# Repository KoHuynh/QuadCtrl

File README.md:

<p align="center">
  <picture>
    <source media="(prefers-color-scheme: dark)" srcset="./images/quadctrl_logo_white_transparent.png">
    
  </picture>
</p>

<p align="center">

  <!-- Laptop app, flight logger, simulation -->
  
  <!-- Hardware & mechanical -->
  
</p>

**A low-cost micro-quadcopter that makes avionics and flight-control education accessible.**

---

QuadCtrl is a ~$30 educational micro-quadcopter designed to teach embedded flight control from the ground up. An ESP32-S3 flight controller fuses LSM6DSV IMU data with a complementary filter and runs a cascaded angle → rate PID loop at 500 Hz to drive four 8520 brushed motors. A custom ESP-NOW transmitter with an OLED display and potentiometers lets you tune PID gains live, in flight. A VL53L0X/VL53L1X time-of-flight sensor adds altitude hold, and optical flow and UWB positioning are planned for autonomous flight without motion capture.

---

# Contents

- [Features](#features)
- [Hardware](#hardware)
- [Electronics](#electronics)
- [Flight Control Algorithm](#flight-control-algorithm)
  - [1. Feedback Control Basics](#1-feedback-control-basics)
  - [2. Attitude Estimation](#2-attitude-estimation)
  - [3. Pilot Commands and Motor Mixing](#3-pilot-commands-and-motor-mixing)
  - [4. Cascaded PID Control](#4-cascaded-pid-control)
  - [5. Altitude Hold](#5-altitude-hold)
- [Roadmap](#roadmap)
- [Acknowledgments](#acknowledgments)

---

# Features

- **500 Hz cascaded PID control**: an outer angle loop feeds an inner rate loop on roll and pitch, with heading hold on yaw
- **Complementary-filter attitude estimation**, with low-pass filtering on the gyro and accelerometer
- **Custom ESP-NOW transmitter** with live PID tuning (potentiometers), flight trim, an OLED telemetry display, and arming safety
- **Altitude hold** using a downward-facing time-of-flight sensor fused with the accelerometer
- **Safety features**: link-loss failsafe (auto-land in altitude mode), attitude cutoff, low-battery monitoring, and throttle-low arming
- **Low cost and simple to build**: off-the-shelf parts, a custom shield PCB, and a 3D-printed frame

# Hardware

| Component | Details |
|---|---|
| Microcontroller | ESP32-S3 dev board (EnVision Maker Studio) with a custom drone shield |
| IMU | LSM6DSV 6-axis accelerometer + gyroscope (I²C) |
| Motors | 4 × 8520 coreless brushed DC motors |
| Propellers | 75 mm |
| Battery | 1S LiPo (660 mAh), roughly 5–7 minutes of flight |
| Height sensor | VL53L0X / VL53L1X time-of-flight (auto-detected) |
| Frame | 3D-printed motor-mount frame |
| Weight | ~75 g |
| Radio | ESP-NOW (2.4 GHz) to a custom ESP32-S3 transmitter |

---

# Electronics

The full shield schematic is available here: [ECE193HQuadCopterShieldSchematicV1.pdf](./images/ECE193HQuadCopterShieldSchematicV1.pdf)

Each motor is driven by a low-side MOSFET switch. The key components are:

- **N-channel MOSFET**: acts as a voltage-controlled switch. When the ESP32 drives the gate HIGH (e.g. GPIO 4), the MOSFET turns on and current flows through the motor. Motor speed is set by the PWM duty cycle (20 kHz).
- **Gate pull-down resistor (10 kΩ)**: holds the MOSFET off whenever the gate is not being actively driven, such as during boot or reset, so the motors cannot spin unexpectedly.
- **Flyback diode (Schottky)**: a motor winding is an inductor, and its current cannot change instantaneously. When the MOSFET switches off, the diode gives that current a safe path to circulate back through the motor and decay. Without it, the resulting voltage spike could destroy the MOSFET. A Schottky diode is used because it switches fast enough to keep up with the PWM.
- **Bulk capacitor (220 µF)**: the motors draw large current bursts, especially at start-up. The battery and its wiring cannot respond instantly, so the bulk capacitor supplies these bursts locally and limits supply dips that could brown out the microcontroller.
- **Bypass capacitor (1 µF)**: shunts high-frequency noise generated by the motors to ground, keeping the supply clean for the logic and sensors.

Battery monitor: A voltage divider made of two 100 kΩ resistors halves the battery voltage, $V_{sense} = V_{bat}\cdot\frac{R_2}{R_1+R_2} = \frac{V_{bat}}{2}$, so a full 4.2 V cell reads 2.1 V, safely within the ESP32-S3’s ADC range. The firmware multiplies the reading by 2 to recover $V_{bat}$ and drives three status LEDs: green (≥ 3.80 V), yellow (3.50–3.80 V), and red (< 3.50 V, recharge soon). The high resistor values keep the divider’s drain to about 21 µA.

---

# Flight Control Algorithm

This section gives an overview of how QuadCtrl stays level and responds to commands. Some familiarity with feedback control helps, but it is not required.

### 1. Feedback Control Basics

A typical closed-loop system works like this:

1. The **reference** $r(t)$ is the desired output, such as a target angle.
2. A **summing node** compares the reference with the sensor measurement to produce the **error**, $e(t) = r(t) - y(t)$.
3. The **controller** turns the error into a command for the **actuators**. Here, the controller decides how hard each motor should spin.
4. The actuators drive the **plant**: the system being controlled, which here is the drone, with its own mass, inertia, and dynamics.
5. The plant's output (angle, rate, height, …) is measured by the **sensors** and fed back to the summing node. The loop repeats continuously to drive the error toward zero.

### 2. Attitude Estimation

To stay level, the drone must first know its orientation (attitude). The LSM6DSV IMU provides two measurements:

- **Gyroscope**: angular rate (°/s) about each axis. On this board, roll is rotation about the forward (y) axis, pitch is rotation about the right (x) axis, and yaw is rotation about the vertical (z) axis.
- **Accelerometer**: linear acceleration plus gravity, which tells the drone which way is down.

**Calibration.** At power-up the drone must sit still while the firmware measures the gyroscope's resting offset (bias). This offset is subtracted from every later reading. A separate level calibration stores the accelerometer's "level" reference in flash.

**Filtering.** Motor vibration adds noise to both sensors. The gyro rates pass through an 80 Hz second-order Butterworth low-pass filter, and the accelerometer uses the IMU's built-in digital low-pass filter (~24 Hz).

**Gyroscope integration.** Integrating the angular rate gives an angle estimate, the same way integrating velocity gives position:

$$\theta(t) = \theta(0) + \int_0^t \omega(\tau)\,d\tau$$

This estimate is smooth and responds instantly. However, any small bias in $\omega$ is integrated as well, so the angle error grows steadily over time (drift).

**Accelerometer tilt.** At rest, the accelerometer measures only gravity. When the drone tilts, gravity is split across the axes, and trigonometry recovers the tilt angle. This reference never drifts, but it is unreliable over short timescales. Any real acceleration, such as sliding sideways, mixes with gravity and makes the drone appear tilted.

**Complementary filter.** The two estimates have opposite strengths, so they are blended every loop:

$$\theta_k = \alpha\,(\theta_{k-1} + \omega_k\,\Delta t) + (1-\alpha)\,\theta_{\text{accel},k}, \qquad \alpha = \frac{\tau}{\tau + \Delta t}$$

With a time constant $\tau = 2$ s and $\Delta t = 2$ ms, $\alpha \approx 0.999$. Each step, the gyro predicts the new angle, and the estimate is nudged slightly toward the accelerometer's gravity angle. Both sensors contribute at all times rather than handing off. Changes faster than about 2 s come from the gyro, while slow drift is pulled out by the accelerometer.

**Limitation: position.** Gravity gives an absolute reference for *tilt*, but nothing in the IMU gives an absolute reference for *position*. Estimating position means integrating acceleration twice, so errors grow with $t^2$, and the IMU alone cannot tell where the drone is in the room. Holding position requires external sensing such as optical flow or UWB (see [Roadmap](#roadmap)).

### 3. Pilot Commands and Motor Mixing

The transmitter sends stick positions to the drone over ESP-NOW at 50 Hz:

- **Roll / pitch sticks** set a target tilt angle (up to ±20°). Trim adds a small constant offset to cancel a steady drift. For example, if the drone always drifts right, trim adds a slight constant left command.
- **Yaw stick** sets a target turn rate.
- **Throttle** sets the base thrust in manual mode, or the target height in altitude-hold mode.

The controller's corrections are mixed into the four motors (X configuration):

- **Pitch**: speed up one pair (front or rear) and slow the other.
- **Roll**: speed up one side (left or right) and slow the other. For example, to move left, the right-side motors speed up, the drone tilts left, and part of the thrust pushes it left. Once the target tilt is reached, the motors even out to hold that angle.
- **Yaw**: speed up one diagonal pair and slow the other. Diagonal motors spin in the same direction, so this changes the net reaction torque on the frame and rotates it without tilting.

When a correction would push a motor above 100 %, all motors are lowered together (desaturation) so the differences between them, and therefore stability, are preserved.

### 4. Cascaded PID Control

QuadCtrl uses two nested loops per axis rather than one. The gyroscope measures rotation rate directly and quickly, so a fast inner loop can reject disturbances immediately. The slower outer loop only has to decide how fast the drone should rotate toward its target angle. Splitting the job this way is more stable and easier to tune than a single loop.

**Outer loop: angle control (P).** The angle error (target − estimate) is multiplied by a gain to produce a desired rotation rate. With a gain of 3, a nose that is 5° too high commands a 15°/s nose-down rotation. Yaw uses heading hold: the stick moves a heading setpoint, and any heading error, such as from a bump, becomes extra yaw rate that turns the nose back.

**Inner loop: rate control (PID).** Each axis compares the desired rate with the gyro's measured rate:

- **P (proportional)** reacts to the current error: the further off it is, the harder it corrects.
- **I (integral)** accumulates error over time to cancel steady biases such as an off-center battery or a weaker motor.
- **D (derivative)** reacts to how fast the error is changing, damping the response so it doesn't overshoot.

The output is a correction for each axis, expressed as a percentage of motor power, which is sent to the motor mixer. Roll and pitch rate gains can be tuned live from the transmitter's potentiometers.

### 5. Altitude Hold

With a downward-facing time-of-flight sensor, the throttle stick becomes a **height command** (e.g. 10 % → 0.2 m, 100 % → 1.0–1.5 m):

1. **Height estimation**: a vertical complementary filter fuses the accelerometer (fast, but drifts) with the ToF range (slow, noisy, but drift-free). The ToF range is tilt-corrected as $h = r\cos\phi\cos\theta$.
2. **Height → climb rate (P)**: height error is converted into a target vertical speed, limited to 0.5 m/s.
3. **Climb rate → throttle (PI)**: the integral term converges to the hover throttle. It is learned during flight and saved, which also compensates for battery sag automatically.

Altitude mode also includes automatic landing, auto-land on radio link loss, and a controlled descent if the height sensor's readings are lost.

---

# Roadmap

- [x] Stabilized flight with cascaded PID
- [x] Live PID tuning and trim from the transmitter
- [x] Altitude hold (VL53L0X / VL53L1X)
- [ ] Optical flow velocity hold (PMW3901) to eliminate horizontal drift
- [ ] UWB positioning (DWM3000) for waypoint navigation without motion capture
- [ ] Multi-drone coordinated flight
- [ ] ToF Ring Sensor -> SLAM
- [ ] Brushless Motor Version for more stable outdoor flight
- [ ] GPS, RTK -> Drone Shows w/ RGB Lights Add-On

### Time-of-Flight Rangefinder: Indoor Altitude Hold

A ToF sensor fires short pulses of invisible (940 nm, eye-safe) infrared laser light at the floor and measures how long the reflection takes to return. Since light travels at a known speed, the round-trip time gives the distance:

$$d = \frac{c \cdot t_{\text{round trip}}}{2}$$

Because the drone tilts while flying, the beam hits the floor at a slant, so the reading is corrected to a true vertical height: $h = d\cos\phi\cos\theta$ (roll $\phi$, pitch $\theta$).

**How it is used:** the ToF height is fused with the accelerometer. The ToF is drift-free but slow and noisy (~30 Hz); the accelerometer is fast but drifts. The result is a smooth height and climb-rate estimate. In altitude-hold mode, the **throttle stick becomes a height command** instead of raw thrust. A height loop converts height error into a target climb rate. A climb-rate PI loop then adjusts throttle around the hover point, and its integral term learns the hover throttle automatically.

**Limits:** range of ~1–2 m (VL53L0X) to ~3–4 m (VL53L1X) indoors. Readings degrade in bright sunlight and over very dark or reflective surfaces. A table or step under the drone looks like a sudden change in height.

---

### Barometer (BMP581): Outdoor Altitude Hold

Air pressure decreases as you climb, by about **12 Pa per meter** near sea level. A barometer measures this pressure, and the change since takeoff gives the height *relative* to the takeoff point:

$$h \approx 44330 \left[1 - \left(\frac{P}{P_0}\right)^{1/5.255}\right] \text{ m}$$

where $P_0$ is the pressure measured on the ground before takeoff.

**Why outdoors:** a ToF sensor runs out of range after a few meters, while a barometer works at any height. The BMP581 resolves height changes of roughly ±0.5 m (or better with filtering), which is fine for holding altitude in open air. As with the ToF, the barometer is fused with the accelerometer for a smooth estimate, and it feeds the same altitude-hold controller.

**Limits:** it measures only relative height, and weather changes slowly shift the reference. Propeller downwash and wind gusts cause pressure noise, so the sensor should be shielded with a small piece of foam. It is much less precise than a ToF sensor close to the ground.

---

### Optical Flow Sensor: Indoor Horizontal Position Hold

An optical flow sensor is a tiny, low-resolution camera that takes hundreds of frames per second. It compares consecutive frames internally and outputs how far the image of the floor has shifted, in pixels ($\Delta x, \Delta y$). Dividing by the time between readings gives **pixels per second**: how fast the floor *appears* to slide past.

Each pixel covers a fixed viewing angle (about 1° on a PMW3901), so this "optical flow" is really an **angular rate**: how many radians per second the floor sweeps across the view. The same ground speed looks slower the higher you fly, just as distant objects seem to move slowly from a car window. **That is why height is required**. Multiplying by the ToF height converts flow into real velocity:

$$v \approx (\omega_{\text{flow}} - \omega_{\text{gyro}}) \cdot h$$

The gyro term is important. When the drone simply tilts in place, the floor *appears* to move even though the drone has not translated, so the measured rotation rate is subtracted first.

**How it is used:** with velocity known, a new outer control loop commands tilt angles that drive horizontal velocity to zero when the sticks are centered. This cancels the slow drift that the IMU alone cannot detect.

**Limits:** it needs a textured, well-lit floor; plain or glossy floors and dim rooms fail. It only works within a limited height range (a PMW3901 needs at least ~8 cm). It measures velocity, not absolute position, so small errors still accumulate into slow wandering over time.

---

### GPS + Magnetometer (u-blox SAM-M10Q): Outdoor Position Hold

Optical flow becomes unreliable at greater heights and over uniform outdoor ground such as grass or pavement. Outdoors, GPS provides an **absolute** position that does not drift over time. This matters for holding position and for coordinating multiple drones.

A **magnetometer** (digital compass) is needed alongside GPS. The gyro's yaw estimate slowly drifts, but to correct a position error the drone must know which way its nose points, so it can decide which direction to tilt. The magnetometer provides that absolute heading.

**Limits:**
- **Accuracy:** a standard module like the [SAM-M10Q](https://www.digikey.com/en/products/detail/u-blox/SAM-M10Q-00B/16672678) is accurate to about **1.5–2 m**. That is fine for a single drone loitering in place, but not for drones flying close together; that requires RTK GPS (centimeter-level).
- **Update rate:** GPS updates slowly (a few Hz), so it is fused with the IMU for smooth control.
- **Magnetic interference:** motor currents and the battery distort the magnetometer, so it must be mounted away from power wiring and calibrated.
- **Weight and wind:** a ~75 g brushed drone struggles in outdoor wind, so outdoor GPS work is best suited to a future **brushless** version of QuadCtrl.

---

### RGB Light Shield: Drone Light Shows

With a ring of RGB LEDs under a translucent diffuser shell, each drone becomes a single glowing "pixel" when seen from a distance at night. With enough drones, each holding a precise position, the swarm can draw shapes and images in the sky.

Beyond the lights themselves, a light show requires:
- **Precise positioning**: RTK GPS (centimeter-level), since standard GPS is too coarse for drones flying meters apart
- **Time synchronization**: every drone must execute its path at exactly the right moment, and GPS conveniently provides an accurate time reference
- **Choreography software**: converts a target image or animation into a collision-free 3D path for each drone
- **Regulatory approval**: in the US, one pilot or ground station operating multiple drones requires an FAA Part 107 waiver (§107.35)

---

### UWB Positioning (DWM3000): Indoor Swarm Flight

Ultra-wideband (UWB) radio is the indoor counterpart to GPS. Several fixed **anchors** are placed around the room, and the drone carries a **tag**. The tag measures its distance to each anchor by timing radio messages, either by two-way ranging or by time-difference-of-arrival. It then trilaterates its position to about **10 cm**, with at least four anchors needed for 3D.

This is the approach used by Bitcraze's Loco Positioning System for the Crazyflie. Because every drone shares the same anchor coordinate frame, UWB enables **indoor waypoint navigation and coordinated multi-drone (swarm) flight** without an expensive motion-capture system.

**Limits:** the anchors must be installed and surveyed, and accuracy degrades when walls or people block the line of sight. Each module adds weight and power draw (~40–55 mA while active). Optical flow is still useful alongside UWB for smooth, low-noise velocity.

---

### Obstacle Sensing (Lidar / Multi-Zone ToF): Toward Autonomous Flight

To navigate autonomously, the drone must sense its surroundings, not just the floor. Options, from heaviest to lightest:

- **2D 360° lidar** (e.g. LD06/LD19, RPLIDAR C1): a spinning laser that measures distance all the way around the drone, producing a horizontal "slice" of the room. These weigh roughly 40–110 g, too much for the current brushed frame, so they suit a larger brushless version.
- **Multiple ToF sensors**: four or five VL53L1X sensors facing front, back, left, right, and up. This is the approach of the Crazyflie **Multi-ranger deck**: lightweight and simple, but with only one distance per direction.

- **Multi-zone ToF (VL53L5CX)**: a single tiny sensor that returns an **8×8 grid of distances** over a ~63° field of view, like a very coarse depth camera.

**2.5D, not 3D:** a 2D lidar combined with the downward ToF height sensor gives a horizontal map of the room plus the drone's altitude. This is often called "2.5D". It is not a full 3D map, so obstacles above or below the scan plane can be missed.

**Toward SLAM:** distance scans combined with motion estimates (optical flow and IMU) are the inputs to **SLAM** (Simultaneous Localization and Mapping). In SLAM, the drone builds a map of an unknown room while tracking its own position within that map. Because SLAM is computationally heavy, it would likely run on a laptop or companion computer, with sensor data streamed from the drone and commands sent back.

---

# Acknowledgments

QuadCtrl was inspired by UCSD's **CSE 176E/276E** course taught by **Professor Steven Swanson**. The goal of this project is to streamline that design around the **EnVision Maker Studio ESP32-S3 dev board**. Several filtering and control ideas, such as the 80 Hz gyro filter and yaw heading hold, were informed by the open-source Crazyflie and LiteWing flight firmware.

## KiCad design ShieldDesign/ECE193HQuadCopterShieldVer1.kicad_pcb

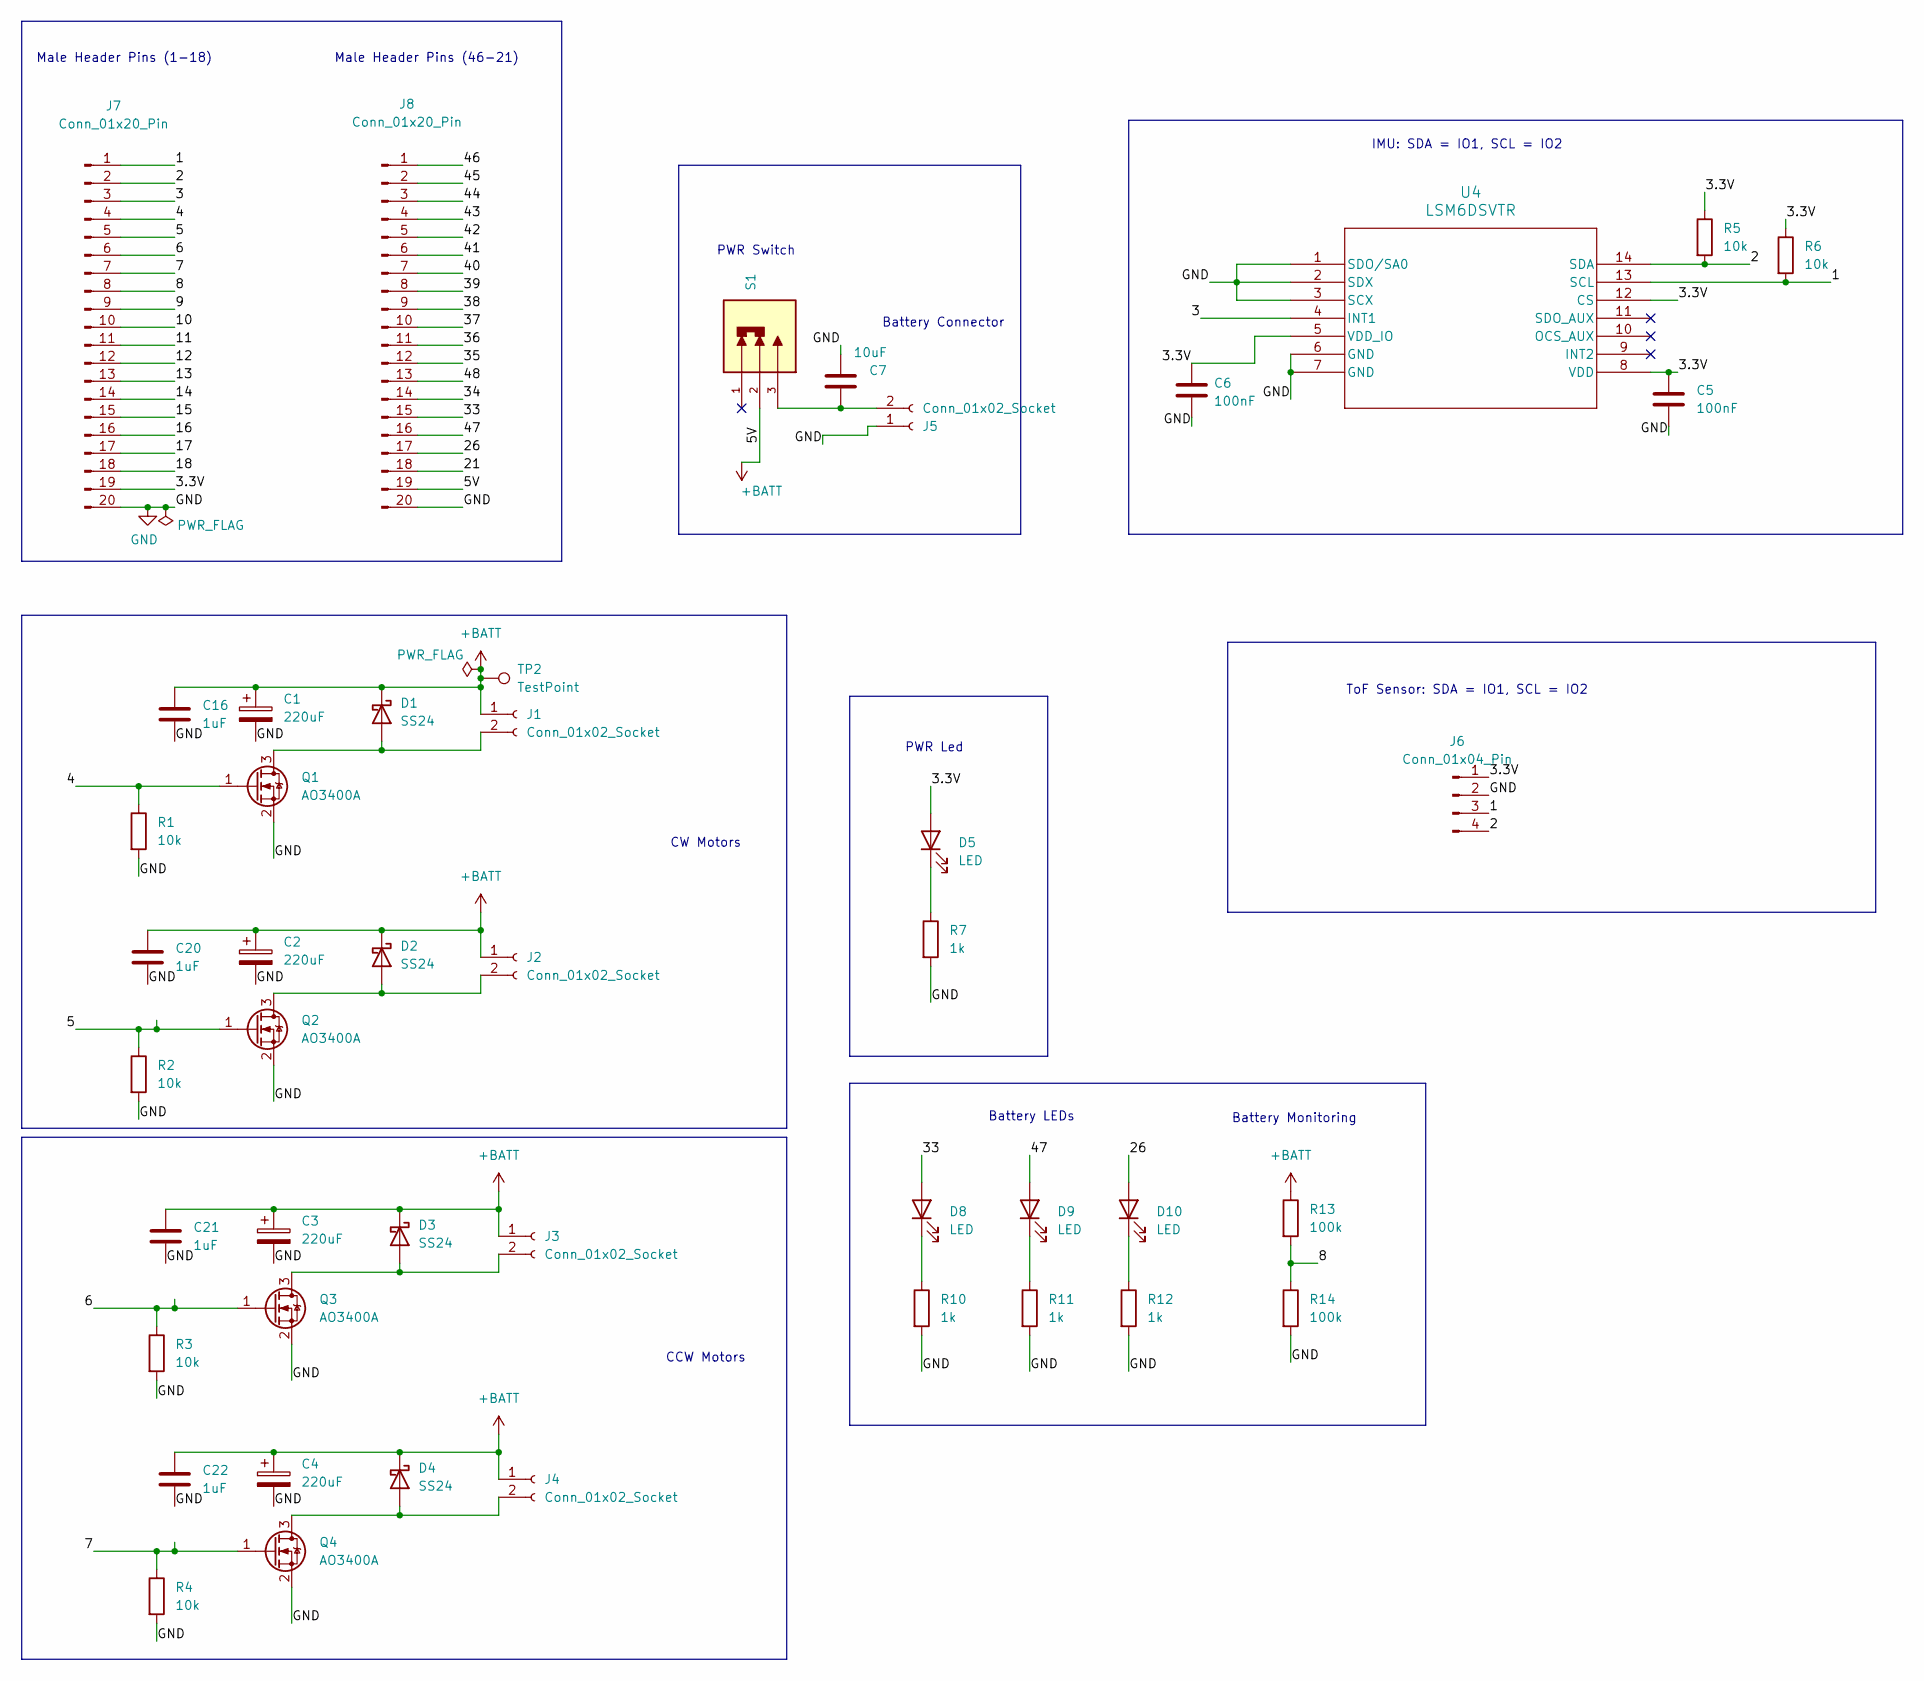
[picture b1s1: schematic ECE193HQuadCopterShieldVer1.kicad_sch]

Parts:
C1, C2, C3, C4: 220uF; CAP_EEEFK1A221SL
C5, C6: 100nF; C_0805_2012Metric_Pad1.18x1.45mm_HandSolder
C7: 10uF; C_0805_2012Metric_Pad1.18x1.45mm_HandSolder
C16, C20, C21, C22: 1uF; C_0805_2012Metric
D1, D2, D3, D4: SS24; D_SMA
D5, D8, D9, D10: LED; LED_0805_2012Metric
J1, J2, J3, J4, J5: Conn_01x02_Socket; PinHeader_1x02_P2.54mm_Vertical
J6: Conn_01x04_Pin; PinHeader_1x04_P2.54mm_Vertical
J7, J8: Conn_01x20_Pin; PinHeader_1x20_P2.54mm_Vertical
Q1, Q2, Q3, Q4: AO3400A; SOT-23
R1, R2, R3, R4, R5, R6: 10k; R_0805_2012Metric_Pad1.20x1.40mm_HandSolder
R7, R10, R11, R12: 1k; R_0805_2012Metric_Pad1.20x1.40mm_HandSolder
R13, R14: 100k; R_0805_2012Metric_Pad1.20x1.40mm_HandSolder
S1: SLW-105558-2A-N-D; SW_SLW-105558-2A-N-D; PARTREV 1.01
TP2: TestPoint; TestPoint_Pad_D1.0mm
U4: LSM6DSVTR; LGA14-L_2P59X3P1X0P5_STM

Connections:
+BATT: C1.1, C2.1, C3.1, C4.1, C16.1, C20.1, C21.1, C22.1, D1.1 (K), D2.1 (K), D3.1 (K), D4.1 (K), J1.1, J2.1, J3.1, J4.1, J8.19, R13.1, S1.2, TP2.1; also elsewhere on the board
/1: J6.3, J7.1, R6.2, U4.13 (SCL)
/2: J6.4, J7.2, R5.2, U4.14 (SDA)
/3: J7.3, U4.4 (INT1)
/3.3V: C5.1, C6.1, D5.2 (A), J6.1, J7.19, R5.1, R6.1, U4.5 (VDD_IO), U4.8 (VDD), U4.12 (CS)
/4: J7.4, Q1.1 (G), R1.1
/5: J7.5, Q2.1 (G), R2.1
/6: J7.6, Q3.1 (G), R3.1
/7: J7.7, Q4.1 (G), R4.1
/8: J7.8, R13.2, R14.1
/9: J7.9
/10: J7.10
/11: J7.11
/12: J7.12
/13: J7.13
/14: J7.14
/15: J7.15
/16: J7.16
/17: J7.17
/18: J7.18
/21: J8.18
/26: D10.2 (A), J8.17
/33: D8.2 (A), J8.15
/34: J8.14
/35: J8.12
/36: J8.11
/37: J8.10
/38: J8.9
/39: J8.8
/40: J8.7
/41: J8.6
/42: J8.5
/43: J8.4
/44: J8.3
/45: J8.2
/46: J8.1
/47: D9.2 (A), J8.16
/48: J8.13
GND: C1.2, C2.2, C3.2, C4.2, C5.2, C6.2, C7.2, C16.2, C20.2, C21.2, C22.2, J5.1, J6.2, J7.20, J8.20, Q1.2 (S), Q2.2 (S), Q3.2 (S), Q4.2 (S), R1.2, R2.2, R3.2, R4.2, R7.2, R10.2, R11.2, R12.2, R14.2, U4.1 (SDO/SA0), U4.2 (SDX), U4.3 (SCX), U4.6 (GND), U4.7 (GND)
unnamed: D1.2 (A), J1.2, Q1.3 (D)
unnamed: D2.2 (A), J2.2, Q2.3 (D)
unnamed: D3.2 (A), J3.2, Q3.3 (D)
unnamed: D4.2 (A), J4.2, Q4.3 (D)
unnamed: D5.1 (K), R7.1
unnamed: D8.1 (K), R10.1
unnamed: D9.1 (K), R11.1
unnamed: D10.1 (K), R12.1
unnamed: C7.1, J5.2, S1.3

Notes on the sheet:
ToF Sensor: SDA = IO1, SCL = IO2
Male Header Pins (46-21)
CW Motors
IMU: SDA = IO1, SCL = IO2
Battery LEDs
PWR Switch
Battery Connector
PWR Led
CCW Motors
Battery Monitoring
Male Header Pins (1-18)

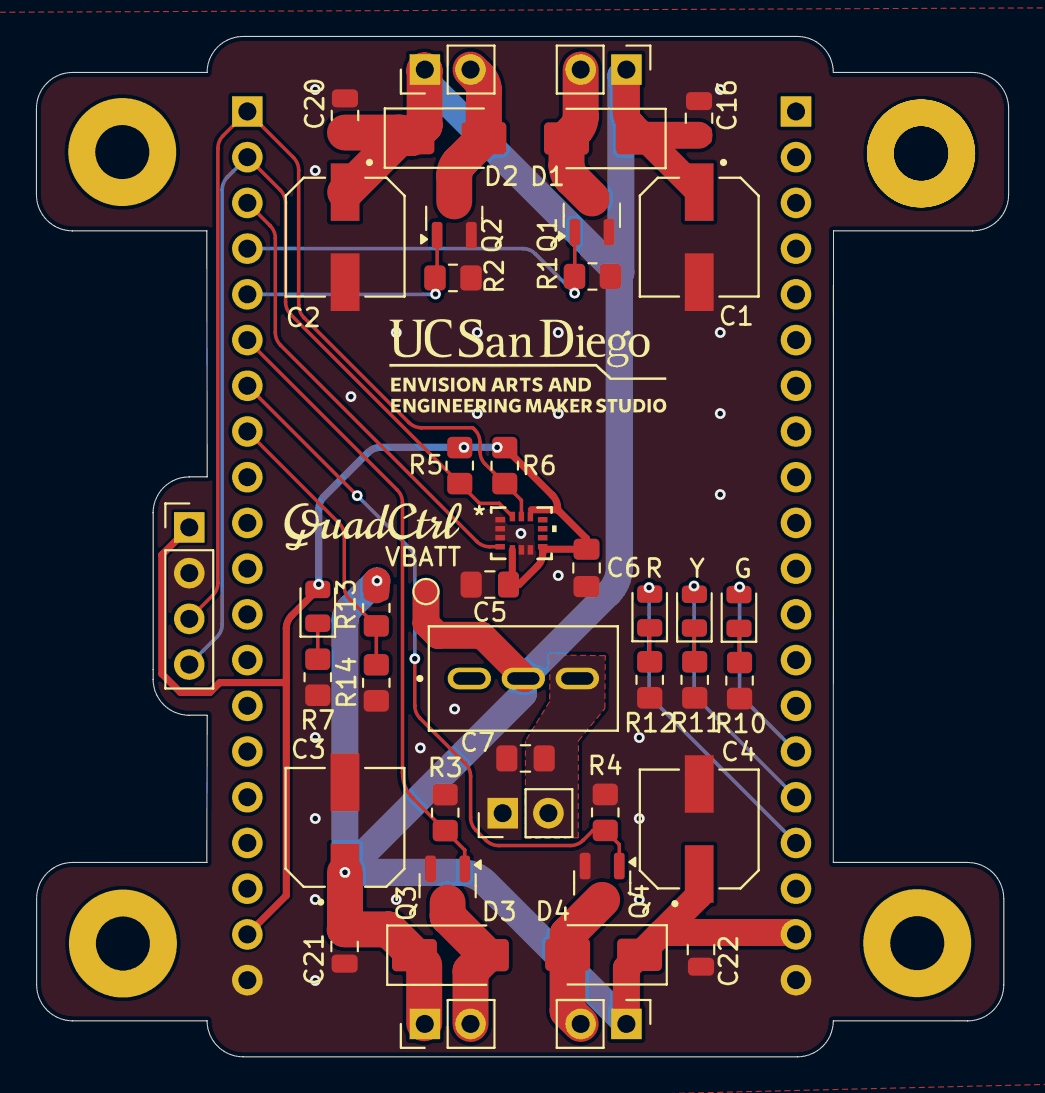
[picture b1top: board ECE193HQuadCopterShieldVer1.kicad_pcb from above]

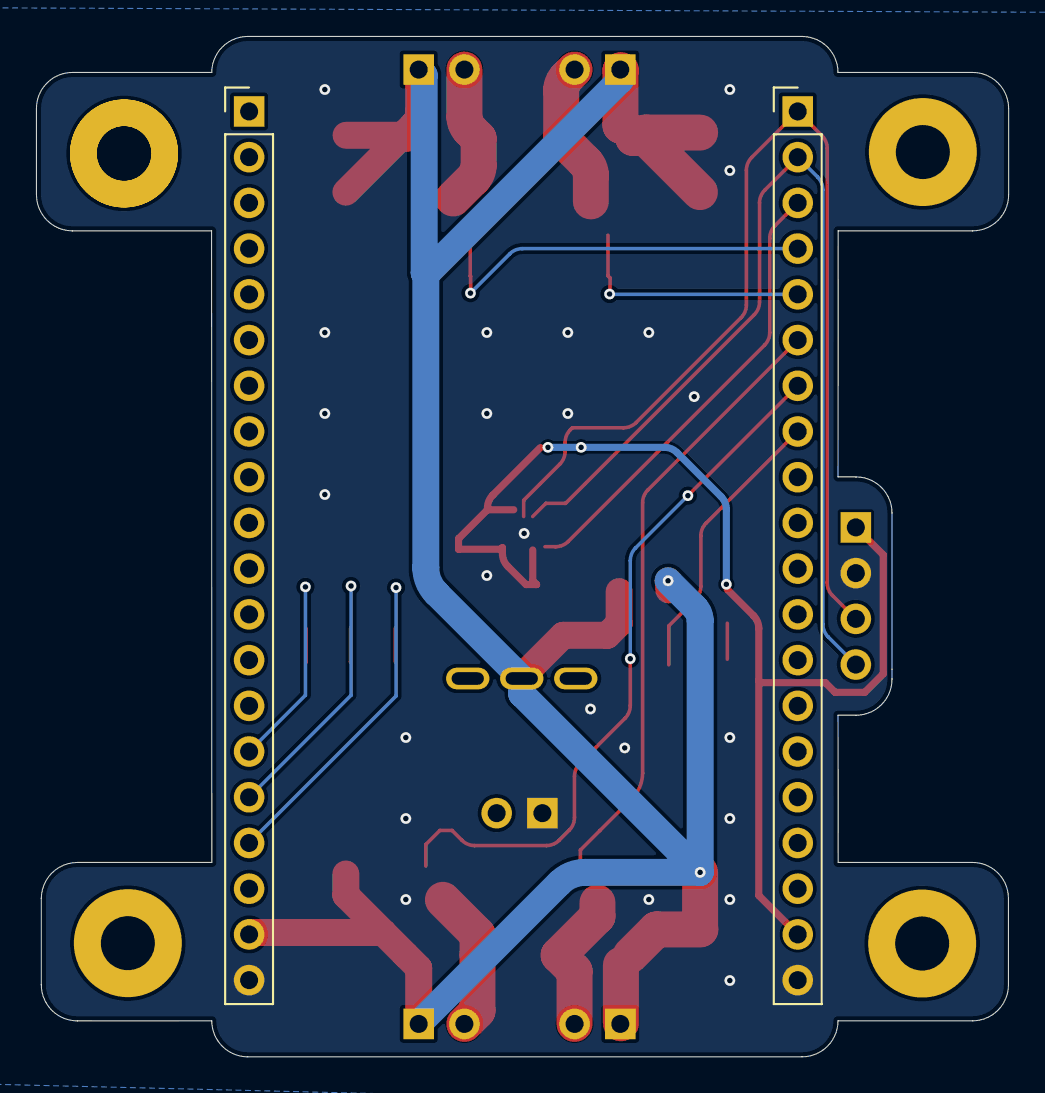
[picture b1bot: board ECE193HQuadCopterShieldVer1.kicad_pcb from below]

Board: 2 copper layers, 54.0 x 56.7 mm, 46 parts (2 on the bottom side), 23 nets.

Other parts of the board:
VBATT: TestPoint; TestPoint_Pad_D1.0mm

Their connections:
+BATT: VBATT.1; also elsewhere on the board
